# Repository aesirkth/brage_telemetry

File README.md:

## Brage Telemetry modem
Brage is a 1W 2.4GHz Telemetry modem that can listen and transmit from a CAN-bus. The name comes from the norse god of poetry, Brage, who will tell the tales of the rocket.

| front | back |
|--------------------|-------------------|
| | |

### Features
* 2Mbit/s
* Time of Flight ranging
* CAN FD with SIC
* UART
* USB
* PCB antenna

### Hardware
The modem is based on an STM32U575CG and an SX1280 transceiver. The radio signal is put through a frontend, filtering and amplifying it to 30dBm. The UART and CAN connectors follow the PixHawk standard while the debugging port is custom.

### Firmware
The firmware is being developed using Rust with Embassy.
See the firmware [README](firmware/README.md)

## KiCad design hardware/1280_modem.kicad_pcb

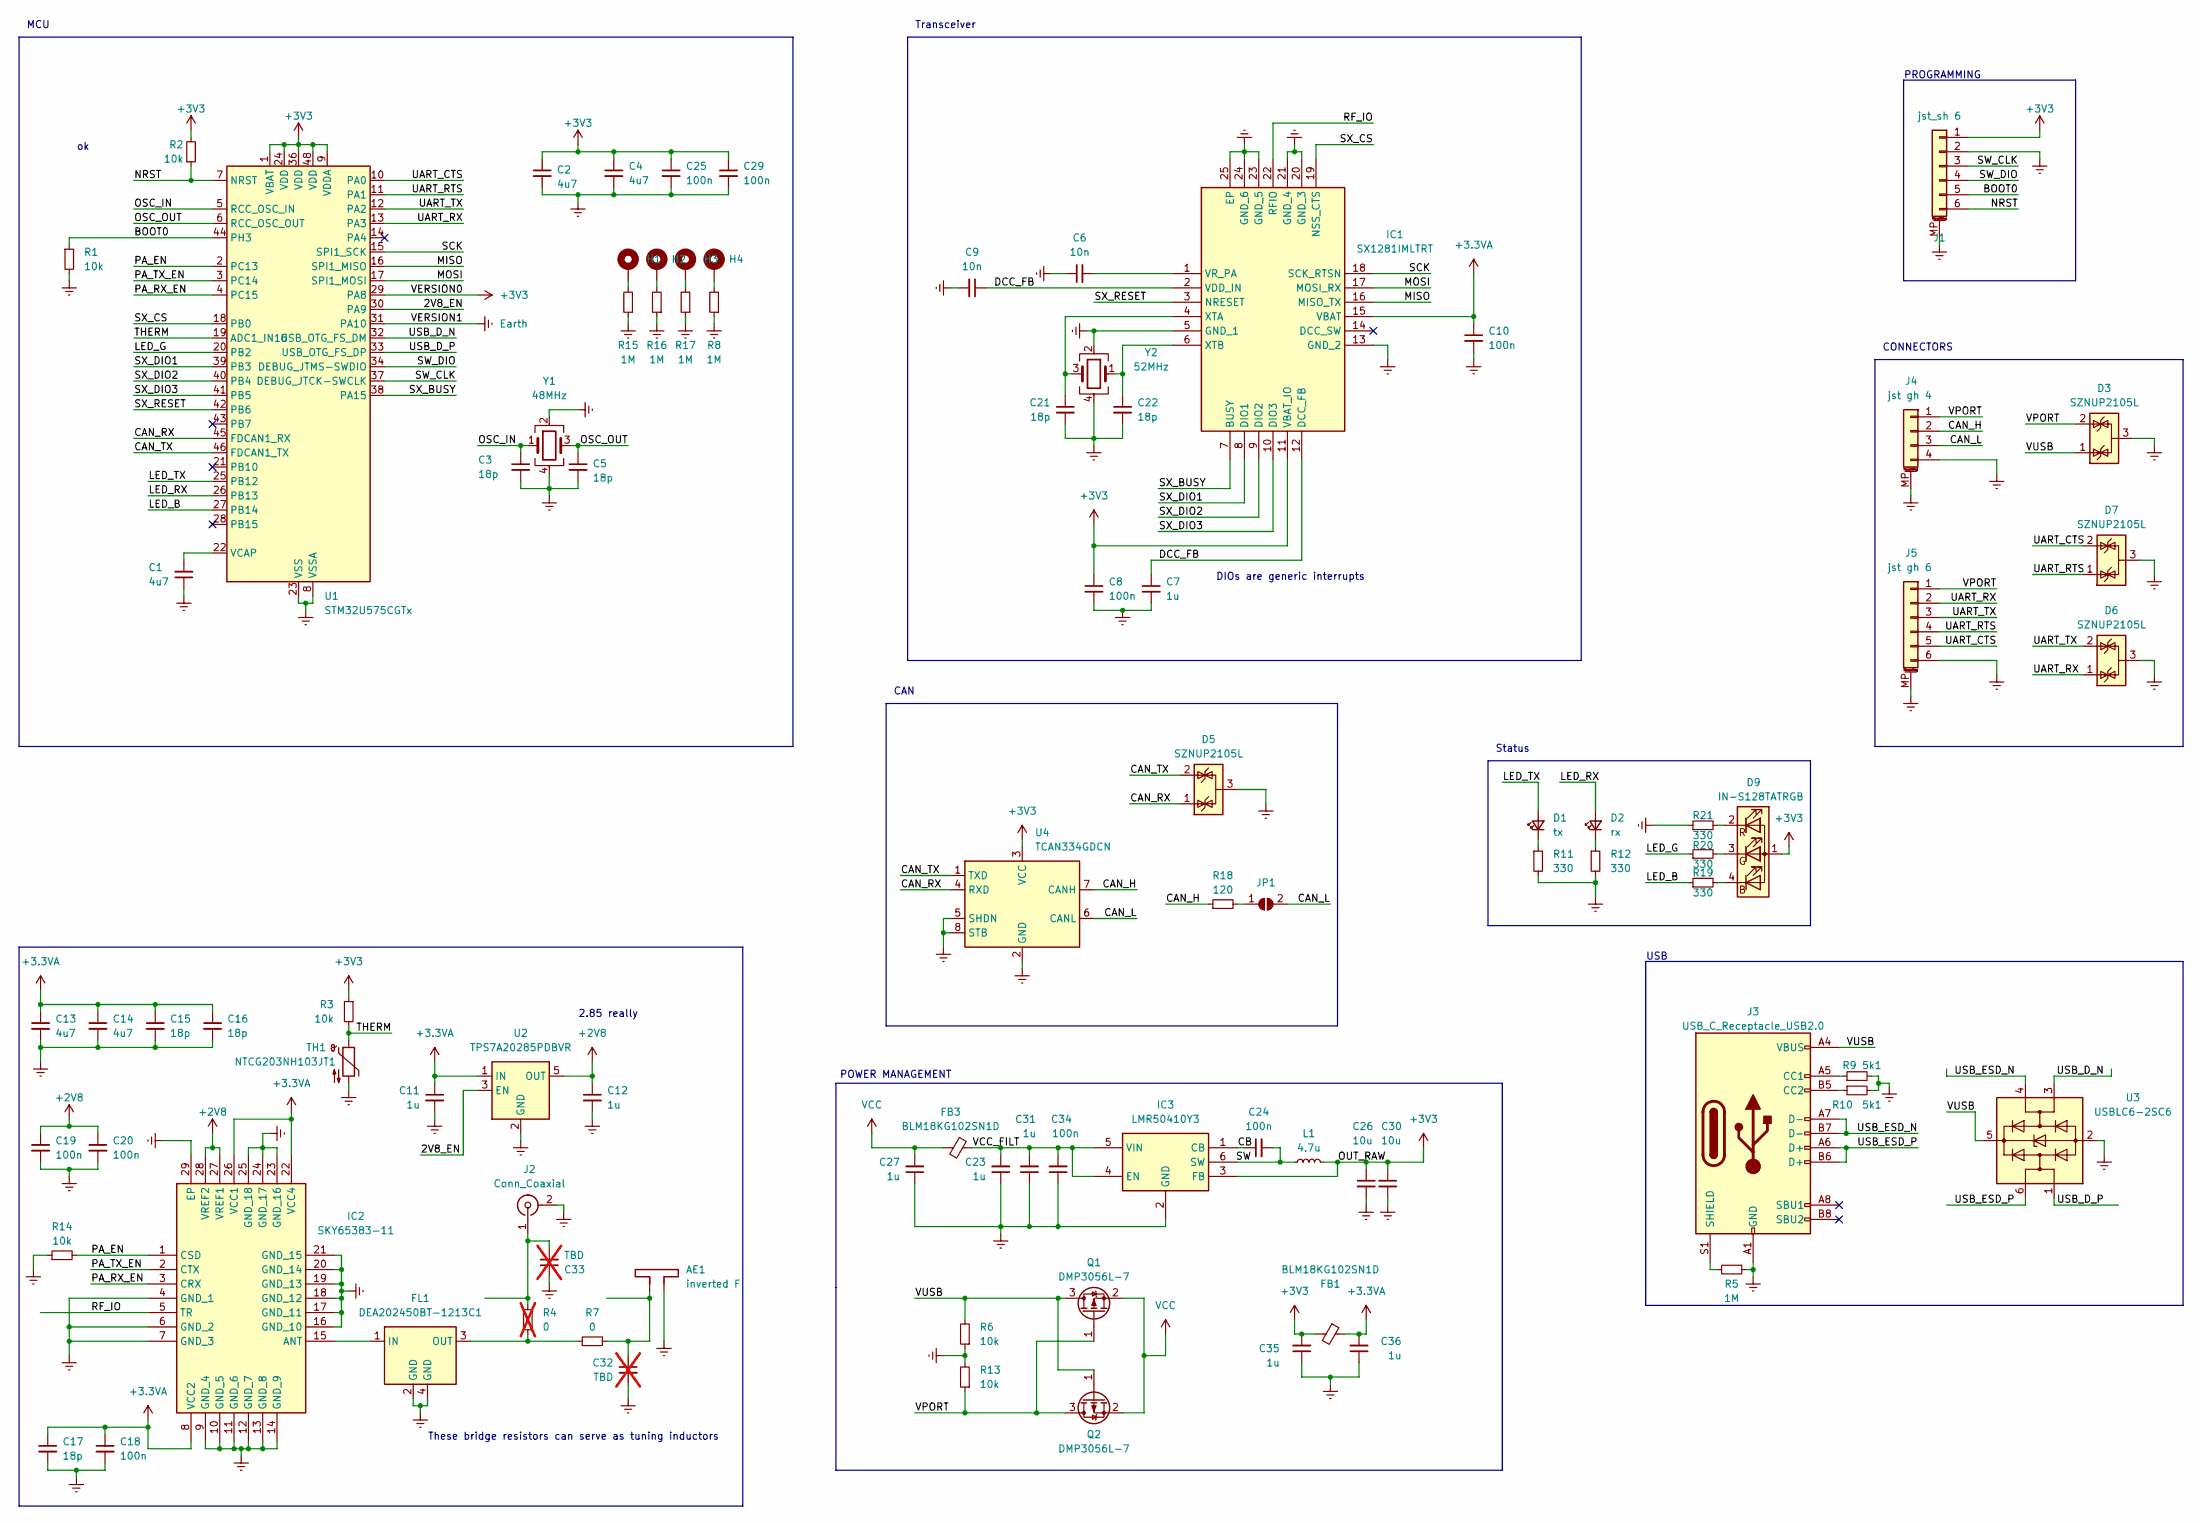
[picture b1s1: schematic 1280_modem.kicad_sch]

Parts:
AE1: inverted F; Texas_SWRA117D_2.4GHz_Left
C1, C2, C4, C13, C14: 4u7; C_0603_1608Metric
C3, C5, C15, C16, C17, C21, C22: 18p; C_0603_1608Metric
C6, C9: 10n; C_0603_1608Metric
C7, C11, C12, C23, C27, C31, C35, C36: 1u; C_0603_1608Metric
C8, C10, C18, C19, C20, C24, C25, C29, C34: 100n; C_0603_1608Metric
C26, C30: 10u; C_0603_1608Metric
C32, C33: TBD; C_0402_1005Metric; not fitted
D1: tx; LED_0805_2012Metric
D2: rx; LED_0805_2012Metric
D3, D5, D6, D7: SZNUP2105L; SOT-23
D9: IN-S128TATRGB; LED_RGB_1210
FB1, FB3: BLM18KG102SN1D; L_0805_2012Metric_Pad1.15x1.40mm_HandSolder
FL1: DEA202450BT-1213C1; DEA202450BT1261A2; Mouser Part Number 810-DEA2024BT1261A2
H1, H2, H3, H4: MountingHole_Pad; MountingHole_3.2mm_M3_Pad_Via
IC1: SX1281IMLTRT; QFN50P400X400X100-25N-D; Mouser Part Number 947-SX1281IMLTRT
IC2: SKY65383-11; SKY6538311; Mouser Part Number 873-SKY65383-11
IC3: LMR50410Y3; SOT95P280X145-6N; Mouser Part Number 595-LMR50410YQDBVRQ1
J1: jst_sh 6; JST_SH_SM06B-SRSS-TB_1x06-1MP_P1.00mm_Horizontal
J2: Conn_Coaxial; SMA_Amphenol_901-143_Horizontal
J3: USB_C_Receptacle_USB2.0; USB_C_Receptacle_Palconn_UTC16-G
J4: jst gh 4; JST_GH_SM04B-GHS-TB_1x04-1MP_P1.25mm_Horizontal
J5: jst gh 6; JST_GH_SM06B-GHS-TB_1x06-1MP_P1.25mm_Horizontal
JP1: SolderJumper_2_Open; SolderJumper-2_P1.3mm_Open_TrianglePad1.0x1.5mm
L1: 4.7u; L_Wurth_WE-LQSH-3012
Q1, Q2: DMP3056L-7; SOT-23
R1, R2, R3, R6, R13, R14: 10k; R_0603_1608Metric
R4: 0; R_0402_1005Metric; not fitted
R5, R8, R15, R16, R17: 1M; R_0603_1608Metric
R7: 0; R_0402_1005Metric
R9, R10: 5k1; R_0603_1608Metric
R11, R12, R19, R20, R21: 330; R_0603_1608Metric
R18: 120; R_0603_1608Metric
TH1: NTCG203NH103JT1; R_0805_2012Metric_Pad1.20x1.40mm_HandSolder
U1: STM32U575CGTx; LQFP-48_7x7mm_P0.5mm
U2: TPS7A20285PDBVR; SOT-23-5
U3: USBLC6-2SC6; SOT-23-6
U4: TCAN334GDCN; TSOT-23-8
Y1: 48MHz; Crystal_SMD_2016-4Pin_2.0x1.6mm
Y2: 52MHz; Crystal_SMD_2016-4Pin_2.0x1.6mm

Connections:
+2V8: C12.1, C19.1, C20.1, IC2.27 (VREF1), IC2.28 (VREF2), U2.5 (OUT)
+3.3VA: C10.1, C11.1, C13.1, C14.1, C15.1, C16.1, C17.1, C18.1, C36.2, FB1.1, IC1.15 (VBAT), IC2.8 (VCC2), IC2.22 (VCC4), IC2.26 (VCC1), U2.1 (IN)
+3V3: C2.1, C4.1, C8.1, C25.1, C26.1, C29.1, C30.1, C35.2, D9.1 (A), FB1.2, IC1.11 (VBAT_IO), IC3.3 (FB), J1.1, L1.2, R2.2, R3.1, U1.1 (VBAT), U1.9 (VDDA), U1.24 (VDD), U1.29 (PA8), U1.36 (VDD), U1.48 (VDD), U4.3 (VCC)
/2V8_EN: U1.30 (PA9), U2.3 (EN)
/BOOT0: J1.5, R1.1, U1.44 (PH3)
/CAN_H: J4.2, R18.1, U4.7 (CANH)
/CAN_L: J4.3, JP1.2 (B), U4.6 (CANL)
/CAN_RX: D5.1 (K), U1.45 (FDCAN1_RX), U4.4 (RXD)
/CAN_TX: D5.2 (K), U1.46 (FDCAN1_TX), U4.1 (TXD)
/CB: C24.1, IC3.1 (CB)
/DCC_FB: C7.1, C9.1, IC1.2 (VDD_IN), IC1.12 (DCC_FB)
/LED_B: R19.1, U1.27 (PB14)
/LED_G: R20.1, U1.20 (PB2)
/LED_RX: D2.2 (A), U1.26 (PB13)
/LED_TX: D1.2 (A), U1.25 (PB12)
/MISO: IC1.16 (MISO_TX), U1.16 (SPI1_MISO)
/MOSI: IC1.17 (MOSI_RX), U1.17 (SPI1_MOSI)
/NRST: J1.6, R2.1, U1.7 (NRST)
/OSC_IN: C3.1, U1.5 (RCC_OSC_IN), Y1.1
/OSC_OUT: C5.1, U1.6 (RCC_OSC_OUT), Y1.3
/PA_EN: IC2.1 (CSD), R14.2, U1.2 (PC13)
/PA_RX_EN: IC2.3 (CRX), U1.4 (PC15)
/PA_TX_EN: IC2.2 (CTX), U1.3 (PC14)
/RF_IO: IC1.22 (RFIO), IC2.5 (TR)
/SCK: IC1.18 (SCK_RTSN), U1.15 (SPI1_SCK)
/SW: C24.2, IC3.6 (SW), L1.1
/SW_CLK: J1.3, U1.37 (DEBUG_JTCK-SWCLK)
/SW_DIO: J1.4, U1.34 (DEBUG_JTMS-SWDIO)
/SX_BUSY: IC1.7 (BUSY), U1.38 (PA15)
/SX_CS: IC1.19 (NSS_CTS), U1.18 (PB0)
/SX_DIO1: IC1.8 (DIO1), U1.39 (PB3)
/SX_DIO2: IC1.9 (DIO2), U1.40 (PB4)
/SX_DIO3: IC1.10 (DIO3), U1.41 (PB5)
/SX_RESET: IC1.3 (NRESET), U1.42 (PB6)
/THERM: R3.2, TH1.1, U1.19 (ADC1_IN16)
/UART_CTS: D7.2 (K), J5.5, U1.10 (PA0)
/UART_RTS: D7.1 (K), J5.4, U1.11 (PA1)
/UART_RX: D6.1 (K), J5.2, U1.13 (PA3)
/UART_TX: D6.2 (K), J5.3, U1.12 (PA2)
/USB_D_N: U1.32 (USB_OTG_FS_DM), U3.3 (I/O2)
/USB_D_P: U1.33 (USB_OTG_FS_DP), U3.1 (I/O1)
/USB_ESD_N: J3.A7 (D-), J3.B7 (D-), U3.4 (I/O2)
/USB_ESD_P: J3.A6 (D+), J3.B6 (D+), U3.6 (I/O1)
/VCC_FILT: C23.2, C31.2, C34.2, FB3.1, IC3.4 (EN), IC3.5 (VIN)
/VPORT: D3.2 (K), J4.1, J5.1, Q1.1 (G), Q2.3 (D), R13.1
/VUSB: D3.1 (K), J3.A4 (VBUS), J3.A9 (VBUS), J3.B4 (VBUS), J3.B9 (VBUS), Q1.3 (D), Q2.1 (G), R6.2, U3.5 (VBUS)
Earth: AE1.2, C1.1, C2.2, C3.2, C4.2, C5.2, C6.1, C7.2, C8.2, C9.2, C10.2, C11.2, C12.2, C13.2, C14.2, C15.2, C16.2, C17.2, C18.2, C19.2, C20.2, C21.2, C22.2, C23.1, C25.2, C26.2, C27.1, C29.2, C30.2, C31.1, C32.2, C33.1, C34.1, C35.1, C36.1, D3.3 (A), D5.3 (A), D6.3 (A), D7.3 (A), FL1.2 (GND), FL1.4 (GND), IC1.5 (GND_1), IC1.13 (GND_2), IC1.20 (GND_3), IC1.21 (GND_4), IC1.23 (GND_5), IC1.24 (GND_6), IC1.25 (EP), IC2.4 (GND_1), IC2.6 (GND_2), IC2.7 (GND_3), IC2.9 (GND_4), IC2.10 (GND_5), IC2.11 (GND_6), IC2.12 (GND_7), IC2.13 (GND_8), IC2.14 (GND_9), IC2.16 (GND_10), IC2.17 (GND_11), IC2.18 (GND_12), IC2.19 (GND_13), IC2.20 (GND_14), IC2.21 (GND_15), IC2.23 (GND_16), IC2.24 (GND_17), IC2.25 (GND_18), IC2.29 (EP), IC3.2 (GND), J1.2, J1.MP (MountPin), J2.2 (Ext), J3.A1 (GND), J3.A12 (GND), J3.B1 (GND), J3.B12 (GND), J4.4, J4.MP (MountPin), J5.6, J5.MP (MountPin), R1.2, R5.1, R6.1, R8.1, R9.2, R10.2, R11.2, R12.2, R13.2, R14.1, R15.1, R16.1, R17.1, R21.1, TH1.2, U1.8 (VSSA), U1.23 (VSS), U1.31 (PA10), U1.35 (VSS), U1.47 (VSS), U2.2 (GND), U3.2 (GND), U4.2 (GND), U4.5 (SHDN), U4.8 (STB), Y1.2, Y1.4, Y2.2, Y2.4
unnamed: AE1.1, C32.1, R7.2
unnamed: D1.1 (K), R11.1
unnamed: D2.1 (K), R12.1
unnamed: D9.4 (BK), R19.2
unnamed: D9.3 (GK), R20.2
unnamed: D9.2 (RK), R21.2
unnamed: FL1.1 (IN), IC2.15 (ANT)
unnamed: FL1.3 (OUT), R4.1, R7.1
unnamed: H1.1, R15.2
unnamed: H2.1, R16.2
unnamed: H3.1, R17.2
unnamed: H4.1, R8.2
unnamed: C6.2, IC1.1 (VR_PA)
unnamed: C21.1, IC1.4 (XTA), Y2.3
unnamed: C22.1, IC1.6 (XTB), Y2.1
unnamed: C33.2, J2.1 (In), R4.2
unnamed: J3.A5 (CC1), R9.1
unnamed: J3.B5 (CC2), R10.1
unnamed: J3.S1 (SHIELD), R5.2
unnamed: JP1.1 (A), R18.2
unnamed: C1.2, U1.22 (VCAP)
VCC: C27.2, FB3.2, Q1.2 (S), Q2.2 (S)

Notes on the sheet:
CAN
2.85 really
PROGRAMMING
Status
POWER MANAGEMENT
MCU
DIOs are generic interrupts
CONNECTORS
USB
These bridge resistors can serve as tuning inductors
Transceiver

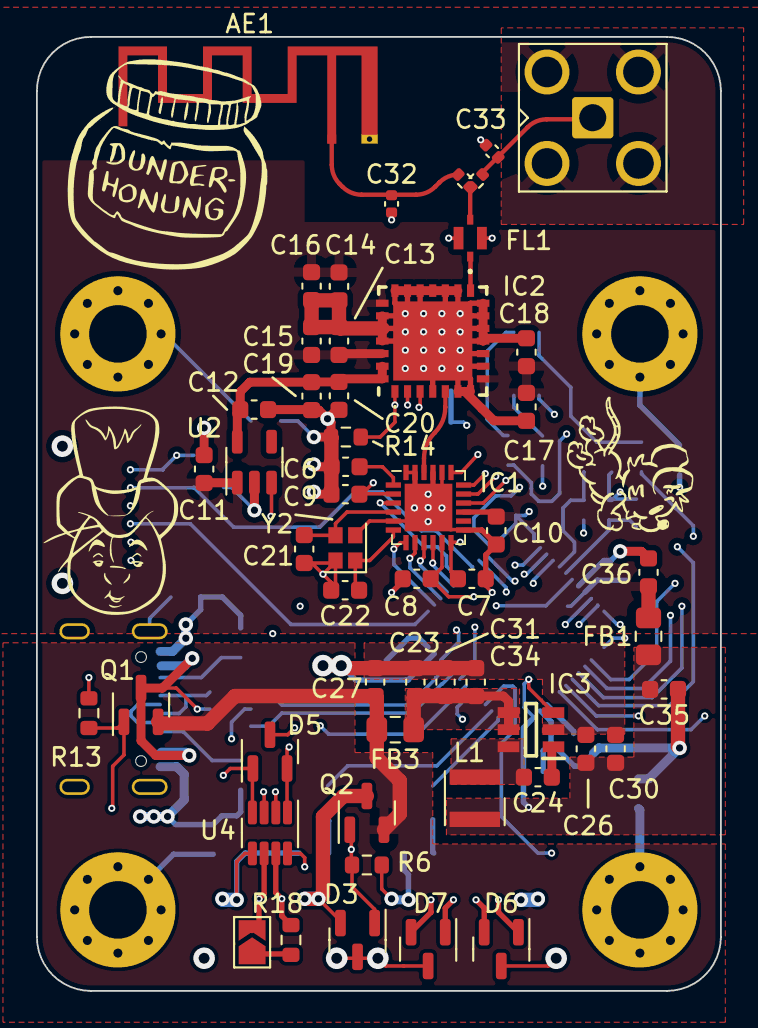
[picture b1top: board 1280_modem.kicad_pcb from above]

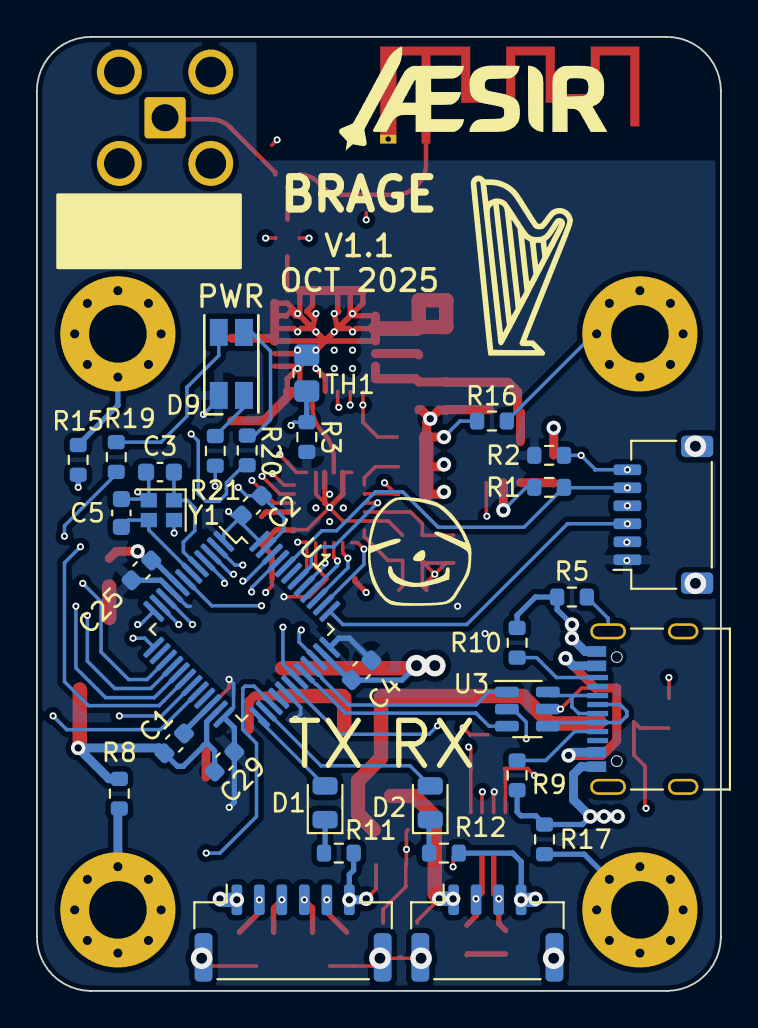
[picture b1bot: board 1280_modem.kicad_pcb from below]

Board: 4 copper layers, 38.0 x 53.0 mm, 90 parts (35 on the bottom side), 69 nets.

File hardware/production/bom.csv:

Designator,Footprint,Quantity,Value,LCSC Part #
AE1,Texas_SWRA117D_2.4GHz_Left,1,inverted F,
"C1, C13, C14, C2, C4",0603,5,4u7,
"C10, C18, C19, C20, C24, C25, C29, C34, C8",0603,9,100n,
"C11, C12, C23, C27, C31, C35, C36, C7",0603,8,1u,
"C15, C16, C17, C21, C22, C3, C5",0603,7,18p,
"C26, C30",0603,2,10u,
"C32, C33",0402,2,TBD,
"C6, C9",0603,2,10n,
D1,0805,1,tx,
D2,0805,1,rx,
"D3, D5, D6, D7",SOT-23,4,SZNUP2105L,
D9,LED_RGB_1210,1,IN-S128TATRGB,
"FB1, FB3",0805,2,BLM18KG102SN1D,
FL1,DEA202450BT1261A2,1,DEA202450BT-1213C1,
"H1, H2, H3, H4",MountingHole_3.2mm_M3_Pad_Via,4,MountingHole_Pad,
IC1,QFN50P400X400X100-25N-D,1,SX1281IMLTRT,
IC2,SKY6538311,1,SKY65383-11,
IC3,SOT95P280X145-6N,1,LMR50410Y3,
J1,JST_SH_SM06B-SRSS-TB_1x06-1MP_P1.00mm_Horizontal,1,jst_sh 6,
J2,SMA_Amphenol_901-143_Horizontal,1,Conn_Coaxial,
J3,USB_C_Receptacle_Palconn_UTC16-G,1,USB_C_Receptacle_USB2.0,
J4,JST_GH_SM04B-GHS-TB_1x04-1MP_P1.25mm_Horizontal,1,jst gh 4,
J5,JST_GH_SM06B-GHS-TB_1x06-1MP_P1.25mm_Horizontal,1,jst gh 6,
JP1,SolderJumper-2_P1.3mm_Open_TrianglePad1.0x1.5mm,1,SolderJumper_2_Open,
L1,L_Wurth_WE-LQSH-3012,1,4.7u,
"Q1, Q2",SOT-23,2,DMP3056L-7,
"R1, R13, R14, R2, R3, R6",0603,6,10k,
"R10, R9",0603,2,5k1,
"R11, R12, R19, R20, R21",0603,5,330,
"R15, R16, R17, R5, R8",0603,5,1M,
R18,0603,1,120,
"R4, R7",0402,2,0,
TH1,0805,1,NTCG203NH103JT1,
U1,LQFP-48_7x7mm_P0.5mm,1,STM32U575CGTx,
U2,SOT-23-5,1,TPS7A20285PDBVR,
U3,SOT-23-6,1,USBLC6-2SC6,
U4,TSOT-23-8,1,TCAN334GDCN,
Y1,Crystal_SMD_2016-4Pin_2.0x1.6mm,1,48MHz,
Y2,Crystal_SMD_2016-4Pin_2.0x1.6mm,1,52MHz,

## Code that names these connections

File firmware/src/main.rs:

#![no_std]
#![no_main]


use defmt::{*};
use defmt_rtt as _;


use embassy_stm32::peripherals::{FDCAN1, USB_OTG_FS, USART2};
use embassy_stm32::time::Hertz;
use embassy_stm32::gpio::{Level, Output, Pull, Speed};
use embassy_stm32::exti::ExtiInput;
use embassy_sync::blocking_mutex::raw::ThreadModeRawMutex;
use embassy_sync::channel::Channel;


use panic_probe as _;

pub mod sx_hal;
pub mod protocol;

pub static UART_IN: Channel<ThreadModeRawMutex, protocol::UartMsg, 32> = Channel::new();
pub static UART_OUT: Channel<ThreadModeRawMutex, protocol::UartMsg, 32> = Channel::new();

pub static CAN_OUT: Channel<ThreadModeRawMutex, protocol::CanMsg, 32> = Channel::new();
pub static CAN_IN: Channel<ThreadModeRawMutex, protocol::CanMsg, 32> = Channel::new();

mod radio;
mod can;
mod uart;

embassy_stm32::bind_interrupts!(struct Irqs {
    OTG_FS => embassy_stm32::usb::InterruptHandler<USB_OTG_FS>;
    FDCAN1_IT0 => embassy_stm32::can::IT0InterruptHandler<FDCAN1>;
    FDCAN1_IT1 => embassy_stm32::can::IT1InterruptHandler<FDCAN1>;
    USART2 => embassy_stm32::usart::BufferedInterruptHandler<USART2>;
});


#[embassy_executor::task]
async fn logger_task(driver: embassy_stm32::usb::Driver<'static, USB_OTG_FS>) -> ! {
    embassy_usb_logger::run!(1024, log::LevelFilter::Trace, driver);
    loop {
        core::panic!("unreachable");
    }
}

#[embassy_executor::main]
async fn main(spawner: embassy_executor::Spawner) {
    let mut config = embassy_stm32::Config::default();
    {
        use embassy_stm32::rcc::*;
        config.rcc.hsi = true;
        config.rcc.hse = Some(Hse {
            freq: Hertz(48_000_000),
            mode: HseMode::Oscillator
        });
        config.rcc.pll1 = Some(Pll {
            source: PllSource::HSE, // 48 MHz
            prediv: PllPreDiv::DIV3, // 16 MHz
            mul: PllMul::MUL10, // 160 MHz
            divp: Some(PllDiv::DIV2),
            divq: Some(PllDiv::DIV2),
            divr: Some(PllDiv::DIV1), // 160 MHz
        });
        config.rcc.sys = Sysclk::PLL1_R;
        config.rcc.voltage_range = VoltageScale::RANGE1;
        config.rcc.hsi48 = Some(Hsi48Config { sync_from_usb: true }); // needed for USB
        config.rcc.mux.iclksel = mux::Iclksel::HSI48; // USB uses ICLK
    }

    let p = embassy_stm32::init(config);

    // Create the driver, from the HAL.
    static mut USB_BUF: core::cell::UnsafeCell<[u8; 1024]> = core::cell::UnsafeCell::new([0; 1024]);
    let mut config = embassy_stm32::usb::Config::default();
    config.vbus_detection = false;
    let usb_driver = embassy_stm32::usb::Driver::new_fs(p.USB_OTG_FS, Irqs, p.PA12, p.PA11, unsafe {USB_BUF.get_mut()}, config);
    // spawner.spawn(logger_task(usb_driver)).unwrap();

    info!("Hello World!");

    let sx_cs = Output::new(p.PB0, Level::High, Speed::VeryHigh);
    let sx_reset = Output::new(p.PB6, Level::High, Speed::VeryHigh);
    let sx_dio1 = ExtiInput::new(p.PB3, p.EXTI3, Pull::Down);
    let sx_dio2 = ExtiInput::new(p.PB4, p.EXTI4, Pull::Down);
    let sx_dio3 = ExtiInput::new(p.PB5, p.EXTI5, Pull::Down);
    let sx_busy = ExtiInput::new(p.PA15, p.EXTI15, Pull::Down);

    let led_tx = Output::new(p.PB12, Level::Low, Speed::VeryHigh);
    let led_rx = Output::new(p.PB13, Level::Low, Speed::VeryHigh);

    let pa_en = Output::new(p.PC13, Level::Low, Speed::VeryHigh);
    let pa_tx_en = Output::new(p.PC14, Level::Low, Speed::VeryHigh);
    let pa_rx_en = Output::new(p.PC15, Level::Low, Speed::VeryHigh);
    let vref_en = Output::new(p.PB2, Level::Low, Speed::VeryHigh); // soldered to LED G with a jumper

    let mut can_configurator = embassy_stm32::can::CanConfigurator::new(p.FDCAN1, p.PB8, p.PB9, Irqs);

    can_configurator.set_bitrate(500_000);

    can_configurator.set_fd_data_bitrate(1_000_000, true);

    let can = can_configurator.start(embassy_stm32::can::OperatingMode::NormalOperationMode);

    static mut CAN_TX_BUF: core::cell::UnsafeCell<embassy_stm32::can::TxFdBuf<1024>> = core::cell::UnsafeCell::new(embassy_stm32::can::TxFdBuf::new());
    static mut CAN_RX_BUF: core::cell::UnsafeCell<embassy_stm32::can::RxFdBuf<1024>> = core::cell::UnsafeCell::new(embassy_stm32::can::RxFdBuf::new());

    let can = can.buffered_fd(unsafe{CAN_TX_BUF.get_mut()}, unsafe {CAN_RX_BUF.get_mut()});

    let can_rx = can.reader();
    let can_tx = can.writer();

    let mut spi_config = embassy_stm32::spi::Config::default();
    spi_config.frequency = Hertz(10_000_000);

    let spi = embassy_stm32::spi::Spi::new(p.SPI1, p.PA5, p.PA7, p.PA6, p.GPDMA1_CH0, p.GPDMA1_CH1, spi_config);

    static mut UART_TX_BUF: core::cell::UnsafeCell<[u8; 512]> = core::cell::UnsafeCell::new([0; 512]);
    static mut UART_RX_BUF: core::cell::UnsafeCell<[u8; 512]> = core::cell::UnsafeCell::new([0; 512]);
    let config = embassy_stm32::usart::Config::default();
    let uart = embassy_stm32::usart::BufferedUart::new_with_rtscts(p.USART2, Irqs, p.PA3, p.PA2, p.PA1, p.PA0, unsafe {UART_TX_BUF.get_mut()}, unsafe {UART_RX_BUF.get_mut()}, config).unwrap();

    let (uart_tx, uart_rx) = uart.split();
    spawner.spawn(radio::radio_task(spi, sx_cs, sx_busy, sx_reset, sx_dio1, sx_dio2, sx_dio3, led_tx, led_rx, pa_en, pa_tx_en, pa_rx_en, vref_en)).unwrap();
    spawner.spawn(can::can_reader_task(can_rx)).unwrap();
    spawner.spawn(can::can_writer_task(can_tx)).unwrap();
    spawner.spawn(uart::uart_writer_task(uart_tx)).unwrap();
    spawner.spawn(uart::uart_reader_task(uart_rx)).unwrap();
}

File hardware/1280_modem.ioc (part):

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Mcu.Name=STM32U575CGTx
Mcu.Package=LQFP48
Mcu.UserName=STM32U575CGTx
PA0.Signal=USART2_CTS
PA1.Signal=USART2_RTS
PA10.Signal=USART1_RX
PA11.Mode=Device_Only
PA11.Signal=USB_OTG_FS_DM
PA12.Mode=Device_Only
PA12.Signal=USB_OTG_FS_DP
PA2.Signal=USART2_TX
PA3.Signal=USART2_RX
PA5.Signal=SPI1_SCK
PA6.Signal=SPI1_MISO
PA7.Signal=SPI1_MOSI
PA9.Signal=USART1_TX
PB0.Signal=SPI1_NSS
PB3\ (JTDO/TRACESWO).Signal=USART1_RTS
PB4\ (NJTRST).Signal=USART1_CTS
RCC.HSE_VALUE=16000000
board=custom

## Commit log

2023-11-14 add pdf schematic
2023-11-14 fix drc
2023-11-14 prettier thermal vias
2023-11-14 improvements
2023-11-14 add pdf
2023-11-15 initial readme
2023-11-15 stuff
2023-11-19 prettier schematic
2023-11-27 micro strip and antenna tuning
2024-02-05 better power electronics
2024-02-05 add libraries
2024-02-05 bamse
2024-02-27 second pass
2024-03-11 final 4 layer version
2024-03-12 ordered version
2024-03-13 update pics
2024-03-28 fix bom
2024-03-29 final (?) bom
2024-04-03 initial firmware
2024-04-04 pre async
2024-04-04 remove radio dependency
2024-04-23 async radio
2024-04-24 update docs
2024-04-24 fix image
2024-05-03 ranging first draft
2024-05-03 first data stream draft
2024-05-06 firmware improvements
2025-10-26 v1.1
